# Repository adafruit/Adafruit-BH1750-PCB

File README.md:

## Adafruit BH1750 Light Sensor - STEMMA QT / Qwiic PCB

<a href="http://www.adafruit.com/products/4681"><br/>
Click here to purchase one from the Adafruit shop</a>

PCB files for the Adafruit BH1750 Light Sensor - STEMMA QT / Qwiic. 

Format is EagleCAD schematic and board layout
* https://www.adafruit.com/product/4681

### Description

This is the BH1750 16-bit Ambient Light Sensor from Rohm. Because of how important it is to humans and most other living things, sensing the amount of light in an environment is a common place to get started when learning to work with microcontrollers and sensors. Should we turn up the brightness of our display or dim it to save power? Which direction should your robot move to stay in an area with the most light? Is it day or night? All of these questions can be answered with the help of the BH1750. It's a small, capable and inexpensive light sensor that you can include into your next project to add the detection and measurement of light.

### License

Adafruit invests time and resources providing this open source design, please support Adafruit and open-source hardware by purchasing products from [Adafruit](https://www.adafruit.com)!

Designed by Limor Fried/Ladyada for Adafruit Industries.

Creative Commons Attribution/Share-Alike, all text above must be included in any redistribution. 
See license.txt for additional details.

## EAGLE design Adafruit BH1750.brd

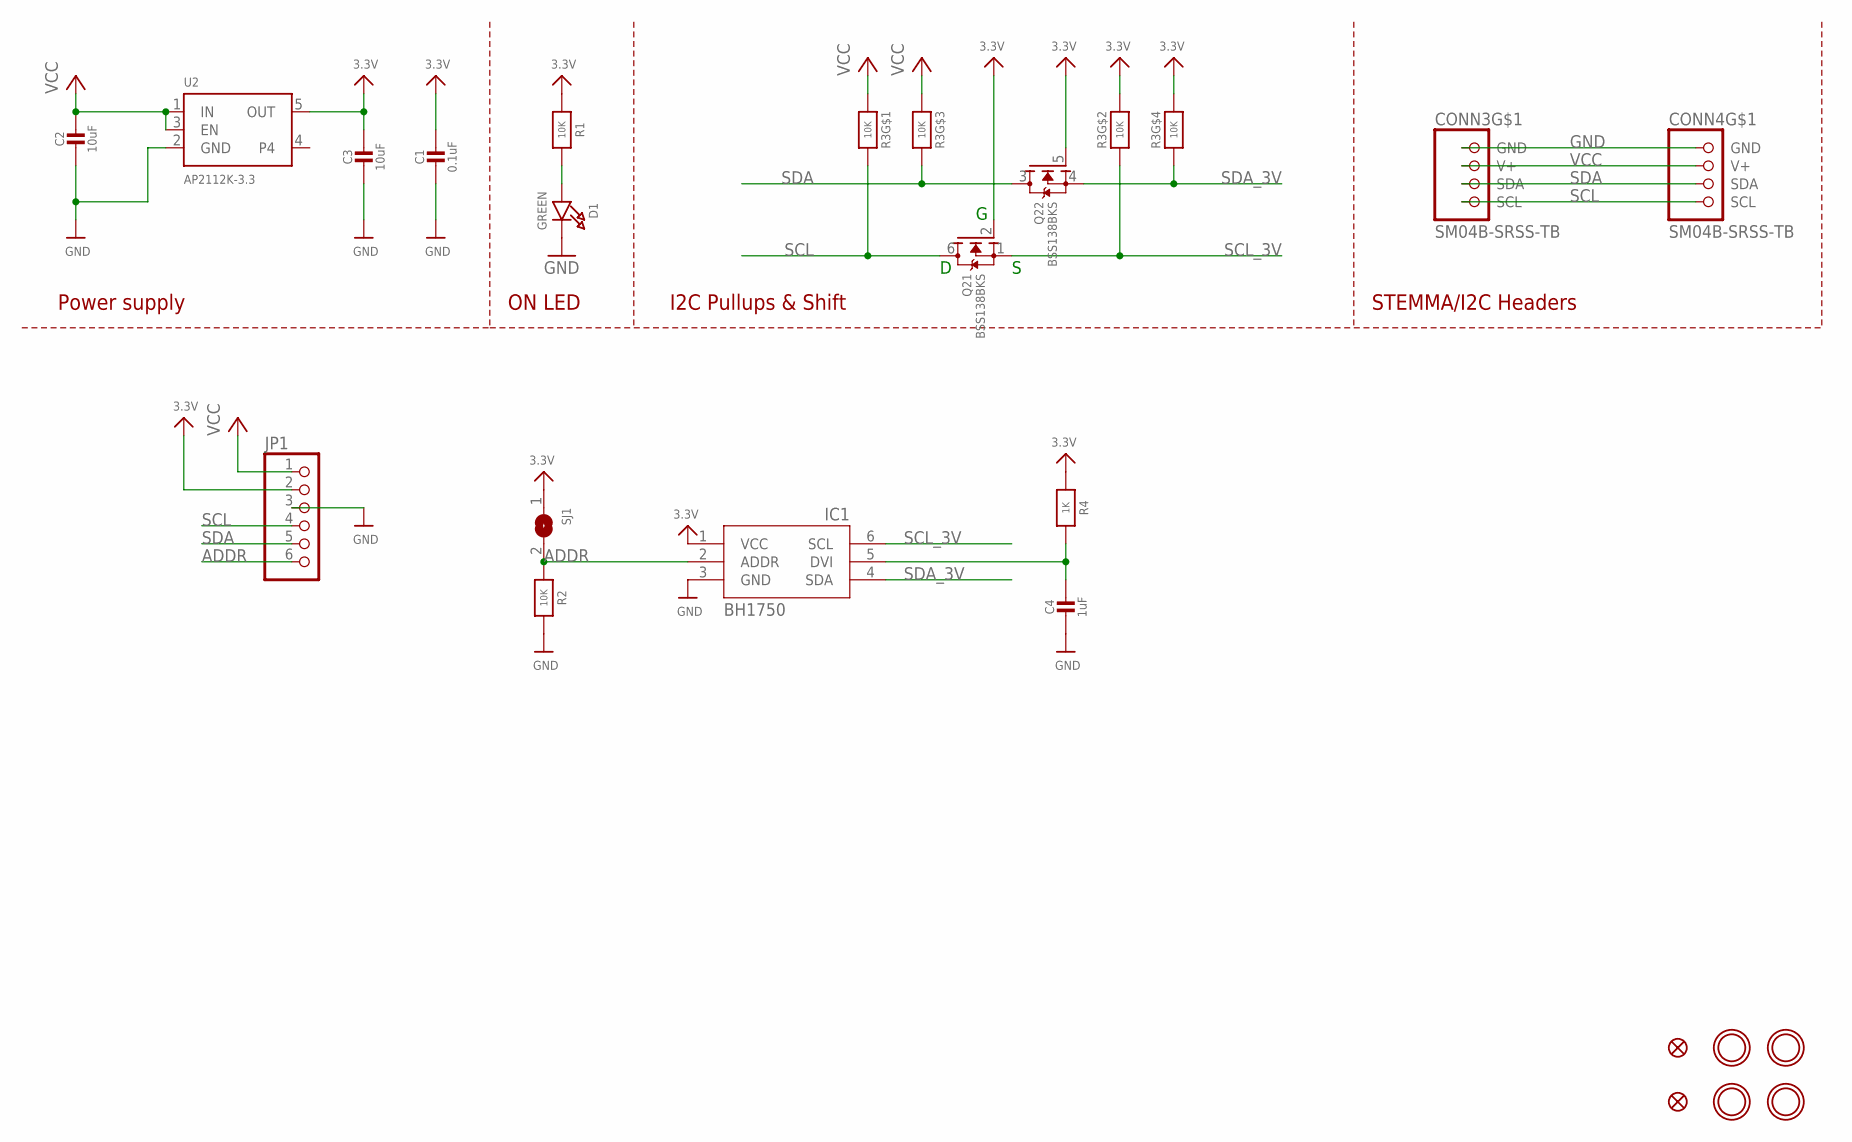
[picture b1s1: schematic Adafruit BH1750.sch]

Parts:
C1: 0.1uF; 0603-NO
C2, C3: 10uF; 0805-NO
C4: 1uF; 0603-NO
CONN3, CONN4: SM04B-SRSS-TB; JST_SH4
D1: GREEN; CHIPLED_0603_NOOUTLINE
FID3, FID4: FIDUCIAL_1MM
IC1: BH1750; WSOF-6
JP1: HEADER-1X670MIL; 1X06_ROUND_70
Q2: BSS138BKS; SOT363
R1, R2: 10K; 0603-NO
R3: 10K; RESPACK_4X0603
R4: 1K; 0603-NO
SJ1: SOLDERJUMPER; SOLDERJUMPER_ARROW_NOPASTE
U2: AP2112K-3.3; SOT23-5
U$1, U$17, U$19, U$21: MOUNTINGHOLE2.5; MOUNTINGHOLE_2.5_PLATED

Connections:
3.3V: C1.1, C3.1, IC1.1 (VCC), JP1.2, Q2.2 (G), Q2.5 (G), R1.1, R3.2 (1), R3.4 (1), R4.1, SJ1.1, U2.5 (OUT)
ADDR: IC1.2 (ADDR), JP1.6, R2.1, SJ1.2
GND: C1.2, C2.2, C3.2, C4.2, CONN3.1 (GND), CONN4.1 (GND), D1.C, IC1.3 (GND), JP1.3, R2.2, U2.2 (GND)
unnamed: D1.A, R1.2
unnamed: C4.1, IC1.5 (DVI), R4.2
SCL: CONN3.4 (SCL), CONN4.4 (SCL), JP1.4, Q2.6 (D), R3.8 (2)
SCL_3V: IC1.6 (SCL), Q2.1 (S), R3.7 (2)
SDA: CONN3.3 (SDA), CONN4.3 (SDA), JP1.5, Q2.3 (D), R3.6 (2)
SDA_3V: IC1.4 (SDA), Q2.4 (S), R3.5 (2)
VCC: C2.1, CONN3.2 (V+), CONN4.2 (V+), JP1.1, R3.1, R3.3 (1), U2.1 (IN), U2.3 (EN)

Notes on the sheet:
I2C Pullups & Shift
STEMMA/I2C Headers
ON LED
Power supply

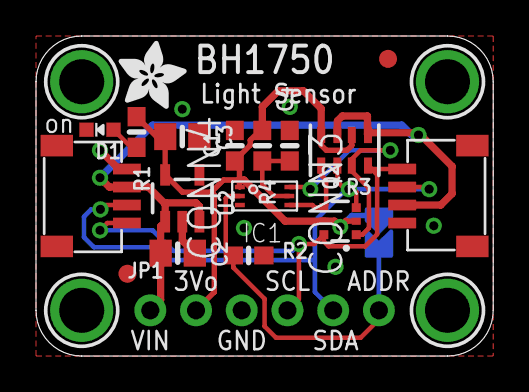
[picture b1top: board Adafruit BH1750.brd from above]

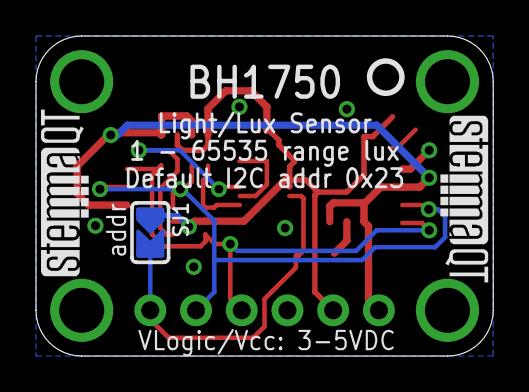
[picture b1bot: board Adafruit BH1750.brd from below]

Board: 2 copper layers, 25.4 x 17.8 mm, 26 parts (4 on the bottom side), 10 nets.

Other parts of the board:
U$22: ADAFRUIT_3.5MM
U$25: PCBFEAT-REV-040
U$30, U$31: STEMMAQT

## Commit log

2020-08-07 Uploading board files

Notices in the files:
parts and their libraries:
microbuilder: This work is placed in the public domain, and may be freely used for commercial and non-commercial work with the following conditions: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
